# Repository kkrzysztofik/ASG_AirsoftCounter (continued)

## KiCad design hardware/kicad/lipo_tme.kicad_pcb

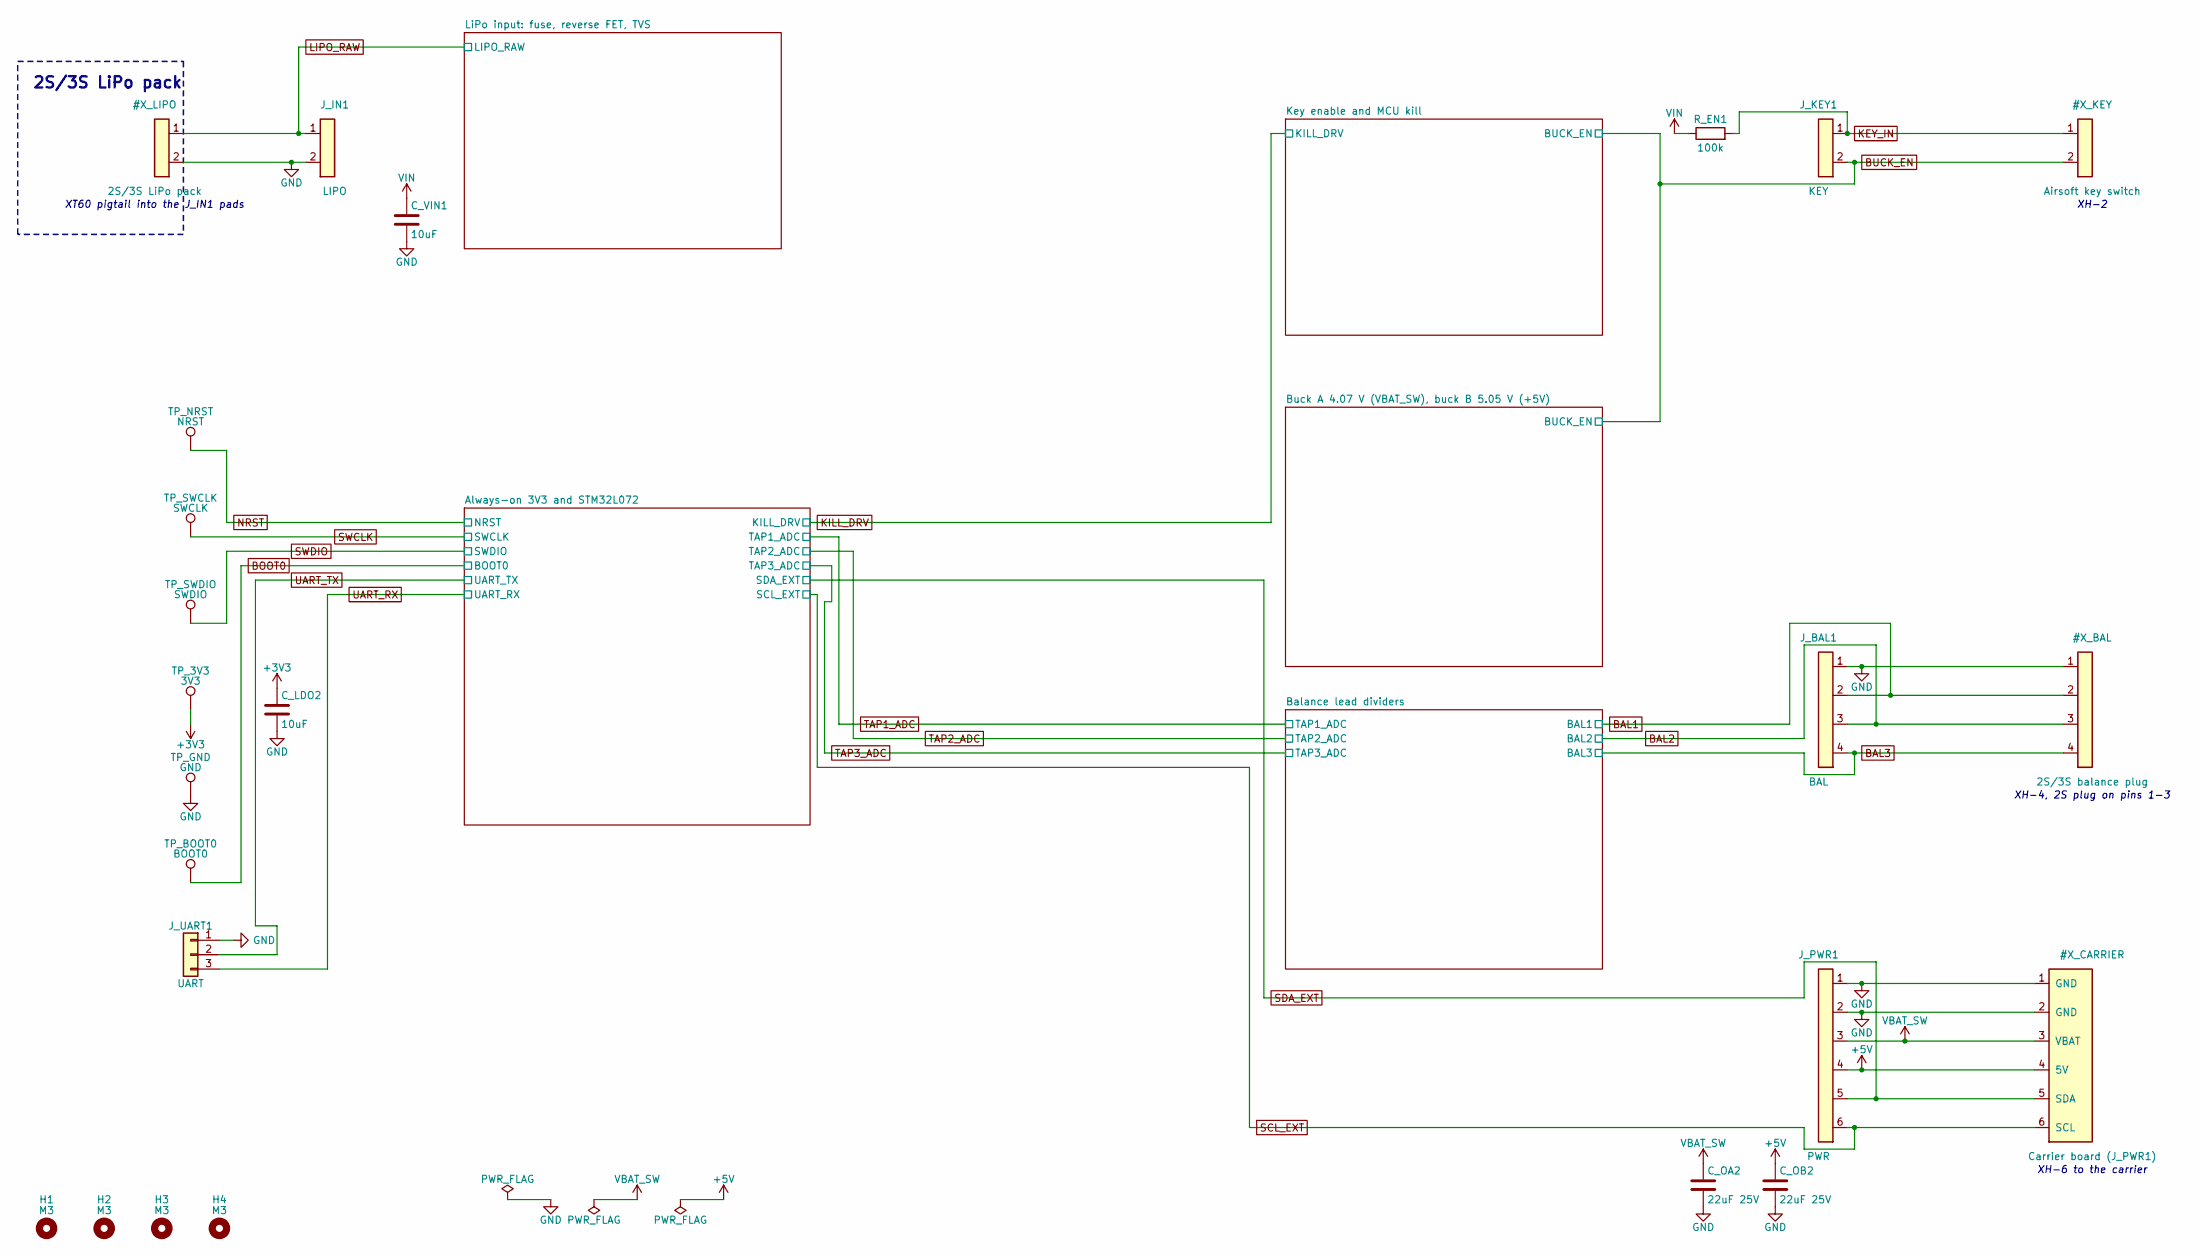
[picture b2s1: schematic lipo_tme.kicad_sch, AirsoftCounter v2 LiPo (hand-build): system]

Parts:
C_LDO2: 10uF; C_0805_2012Metric_Pad1.18x1.45mm_HandSolder
C_OA2: 22uF 25V; C_1206_3216Metric_Pad1.33x1.80mm_HandSolder
C_OB2: 22uF 25V; C_1206_3216Metric_Pad1.33x1.80mm_HandSolder
C_VIN1: 10uF; C_0805_2012Metric_Pad1.18x1.45mm_HandSolder
H1, H2, H3, H4: M3; MountingHole_3.2mm_M3
J_BAL1: BAL; JST_XH_B4B-XH-A_1x04_P2.50mm_Vertical
J_IN1: LIPO; SolderWire-1.5sqmm_1x02_P6mm_D1.7mm_OD3mm
J_KEY1: KEY; JST_XH_B2B-XH-A_1x02_P2.50mm_Vertical
J_PWR1: PWR; JST_XH_B6B-XH-A_1x06_P2.50mm_Vertical
J_UART1: UART; PinHeader_1x03_P2.54mm_Vertical
R_EN1: 100k; R_0805_2012Metric_Pad1.20x1.40mm_HandSolder
TP_3V3: 3V3; TestPoint_Pad_D1.5mm
TP_BOOT0: BOOT0; TestPoint_Pad_D1.5mm
TP_GND: GND; TestPoint_Pad_D1.5mm
TP_NRST: NRST; TestPoint_Pad_D1.5mm
TP_SWCLK: SWCLK; TestPoint_Pad_D1.5mm
TP_SWDIO: SWDIO; TestPoint_Pad_D1.5mm

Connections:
+3V3: C_LDO2.1, TP_3V3.1; also elsewhere on the board
BOOT0: TP_BOOT0.1; also elsewhere on the board
NRST: TP_NRST.1; also elsewhere on the board
SWCLK: TP_SWCLK.1; also elsewhere on the board
SWDIO: TP_SWDIO.1; also elsewhere on the board
UART_RX: J_UART1.3; also elsewhere on the board
UART_TX: J_UART1.2; also elsewhere on the board
VIN: C_VIN1.1, R_EN1.1; also elsewhere on the board

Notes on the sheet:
XH-6 to the carrier
XH-2
XH-4, 2S plug on pins 1-3
XT60 pigtail into the J_IN1 pads
2S/3S LiPo pack

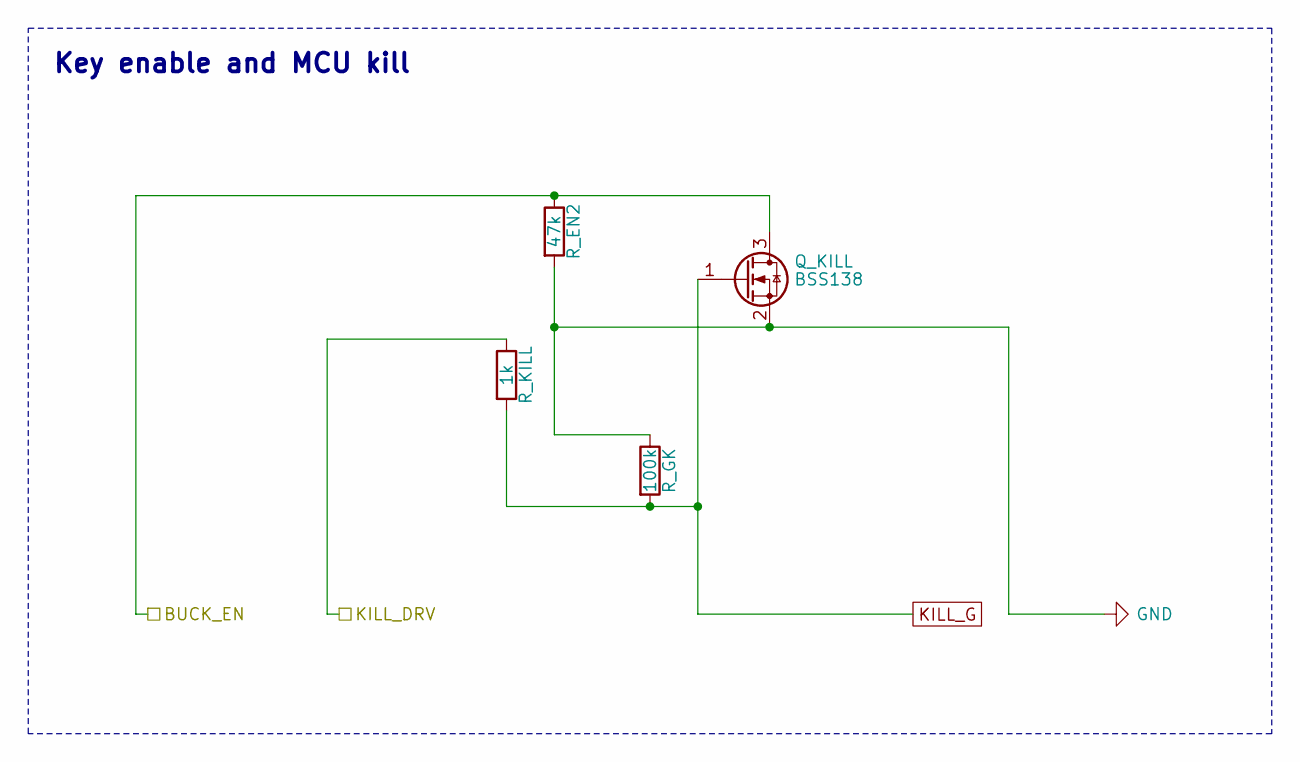
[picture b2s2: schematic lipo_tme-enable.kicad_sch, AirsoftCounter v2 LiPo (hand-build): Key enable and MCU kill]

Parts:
Q_KILL: BSS138; SOT-23
R_EN2: 47k; R_0805_2012Metric_Pad1.20x1.40mm_HandSolder
R_GK: 100k; R_0805_2012Metric_Pad1.20x1.40mm_HandSolder
R_KILL: 1k; R_0805_2012Metric_Pad1.20x1.40mm_HandSolder

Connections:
KILL_DRV: R_KILL.1; also elsewhere on the board
KILL_G: Q_KILL.1 (G), R_GK.2, R_KILL.2

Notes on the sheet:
Key enable and MCU kill

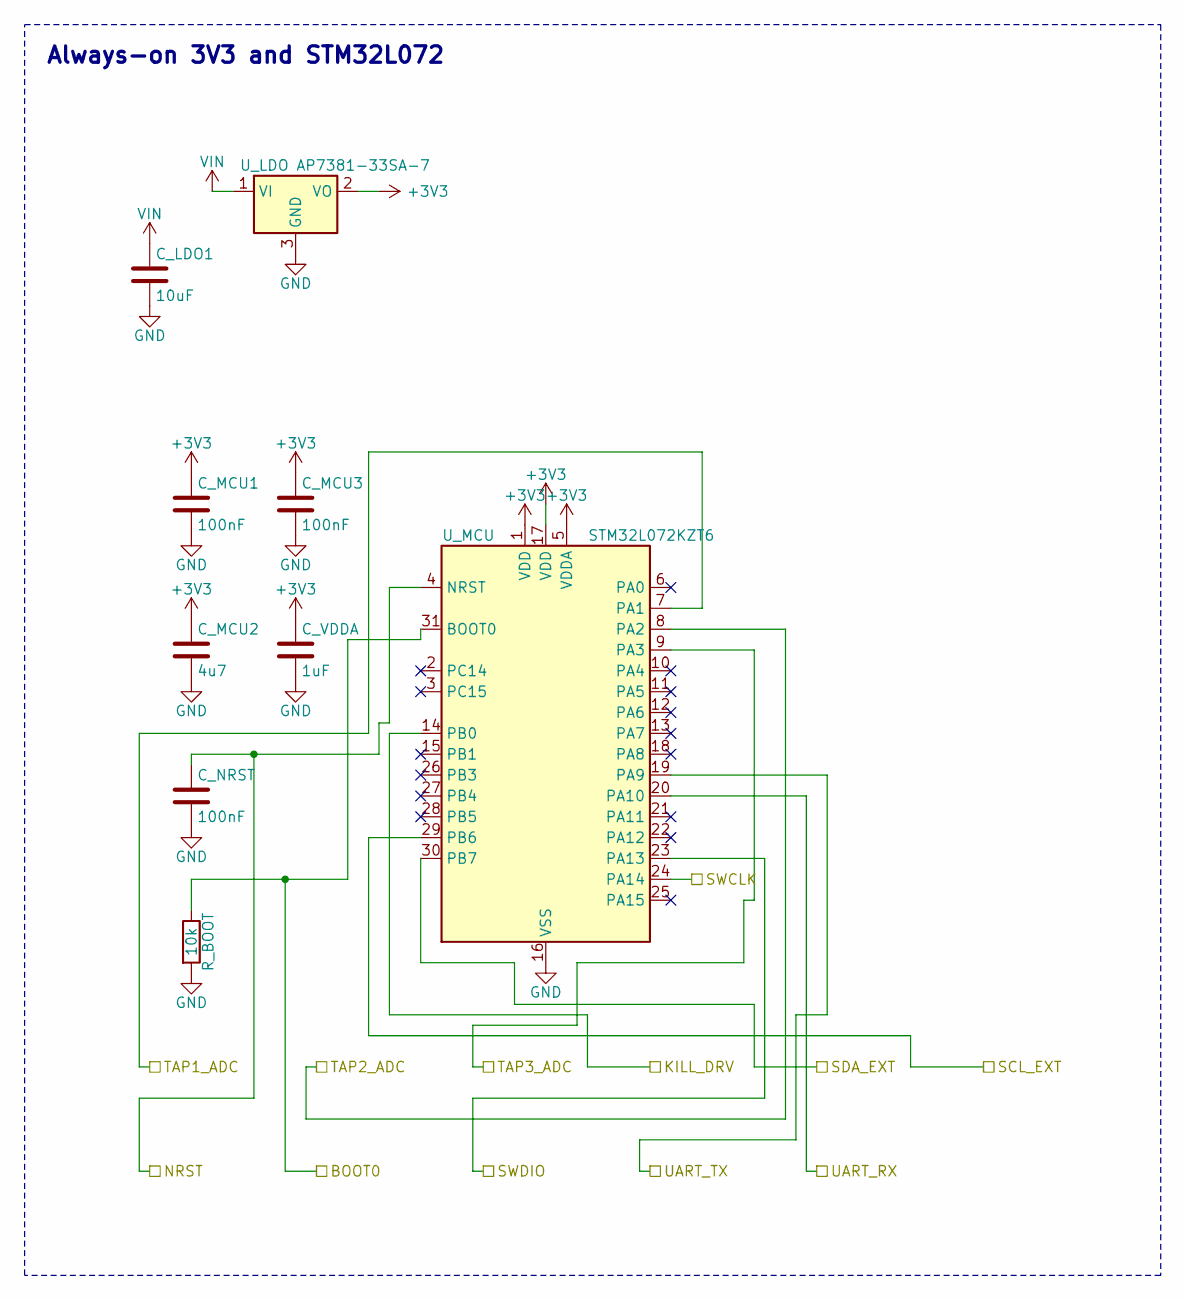
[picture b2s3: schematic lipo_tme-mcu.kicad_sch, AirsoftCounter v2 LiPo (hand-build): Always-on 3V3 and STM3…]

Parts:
C_LDO1: 10uF; C_0805_2012Metric_Pad1.18x1.45mm_HandSolder
C_MCU1, C_MCU3: 100nF; C_0805_2012Metric_Pad1.18x1.45mm_HandSolder
C_MCU2: 4u7; C_0805_2012Metric_Pad1.18x1.45mm_HandSolder
C_NRST: 100nF; C_0805_2012Metric_Pad1.18x1.45mm_HandSolder
C_VDDA: 1uF; C_0805_2012Metric_Pad1.18x1.45mm_HandSolder
R_BOOT: 10k; R_0805_2012Metric_Pad1.20x1.40mm_HandSolder
U_LDO: AP7381-33SA-7; SOT-23
U_MCU: STM32L072KZT6; LQFP-32_7x7mm_P0.8mm

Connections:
+3V3: C_MCU1.1, C_MCU2.1, C_MCU3.1, C_VDDA.1, U_LDO.2 (VO), U_MCU.1 (VDD), U_MCU.5 (VDDA), U_MCU.17 (VDD); also elsewhere on the board
BOOT0: R_BOOT.1, U_MCU.31 (BOOT0); also elsewhere on the board
KILL_DRV: U_MCU.14 (PB0); also elsewhere on the board
NRST: C_NRST.1, U_MCU.4 (NRST); also elsewhere on the board
SWCLK: U_MCU.24 (PA14); also elsewhere on the board
SWDIO: U_MCU.23 (PA13); also elsewhere on the board
TAP1_ADC: U_MCU.7 (PA1); also elsewhere on the board
TAP2_ADC: U_MCU.8 (PA2); also elsewhere on the board
TAP3_ADC: U_MCU.9 (PA3); also elsewhere on the board
UART_RX: U_MCU.20 (PA10); also elsewhere on the board
UART_TX: U_MCU.19 (PA9); also elsewhere on the board
VIN: C_LDO1.1, U_LDO.1 (VI); also elsewhere on the board

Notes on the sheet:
Always-on 3V3 and STM32L072

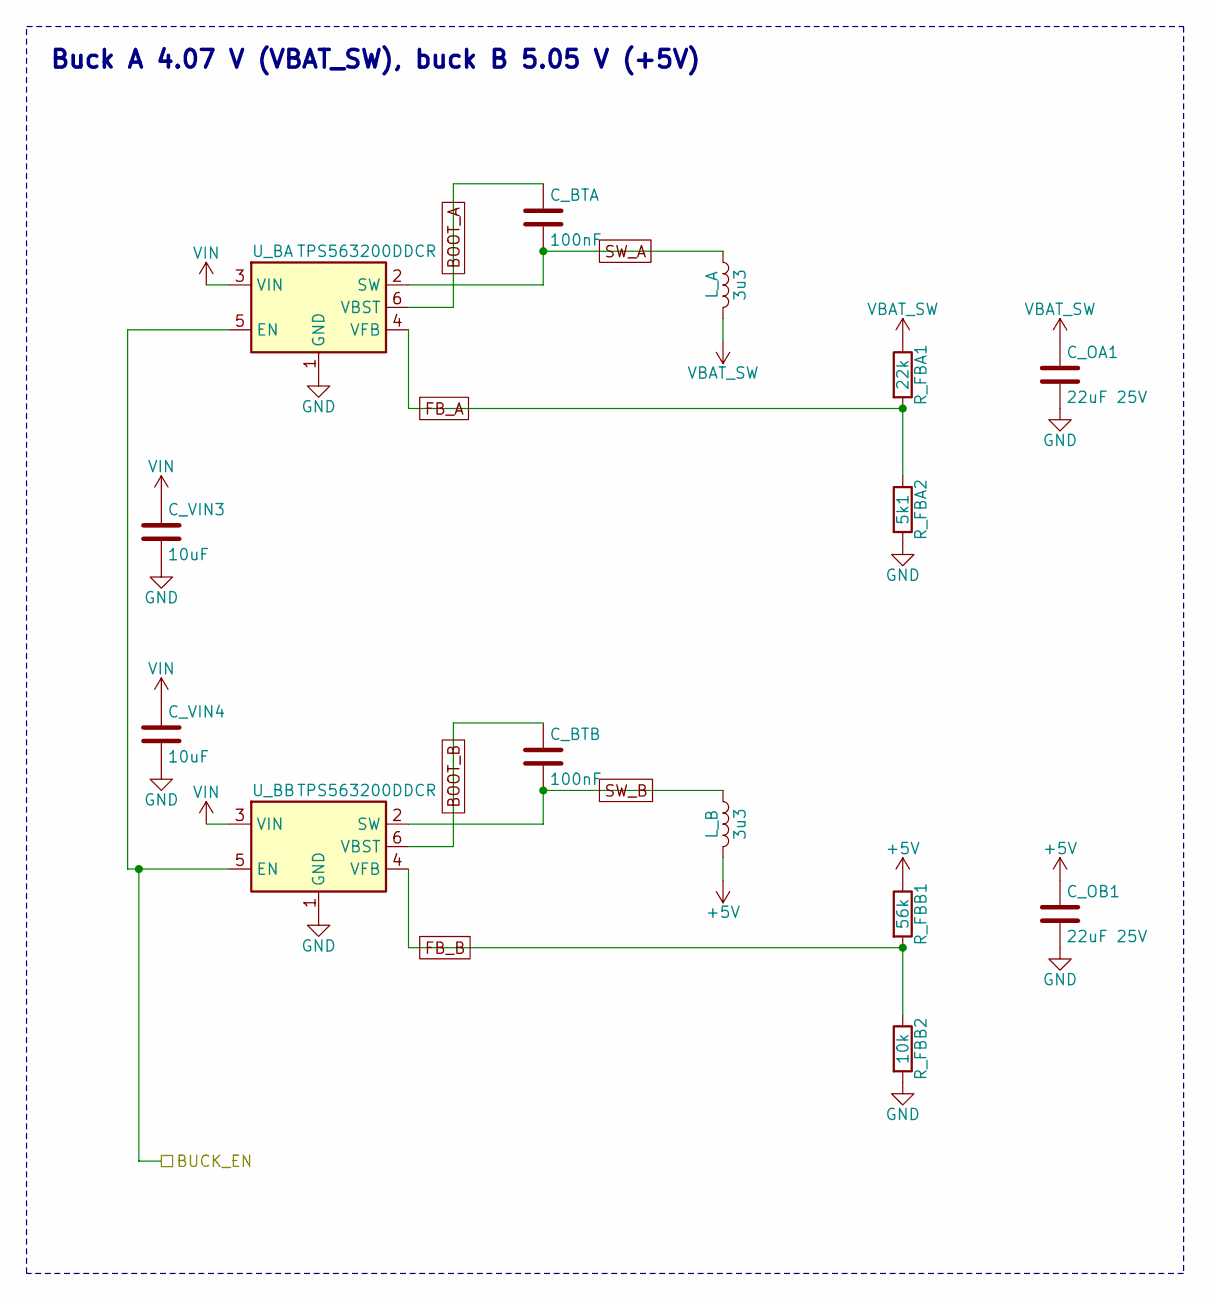
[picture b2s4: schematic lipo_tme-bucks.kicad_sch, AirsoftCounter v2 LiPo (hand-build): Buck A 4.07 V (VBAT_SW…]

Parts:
C_BTA: 100nF; C_0805_2012Metric_Pad1.18x1.45mm_HandSolder
C_BTB: 100nF; C_0805_2012Metric_Pad1.18x1.45mm_HandSolder
C_OA1: 22uF 25V; C_1206_3216Metric_Pad1.33x1.80mm_HandSolder
C_OB1: 22uF 25V; C_1206_3216Metric_Pad1.33x1.80mm_HandSolder
C_VIN3, C_VIN4: 10uF; C_0805_2012Metric_Pad1.18x1.45mm_HandSolder
L_A: 3u3; L_Bourns_SRN6045TA
L_B: 3u3; L_Bourns_SRN6045TA
R_FBA1: 22k; R_0805_2012Metric_Pad1.20x1.40mm_HandSolder
R_FBA2: 5k1; R_0805_2012Metric_Pad1.20x1.40mm_HandSolder
R_FBB1: 56k; R_0805_2012Metric_Pad1.20x1.40mm_HandSolder
R_FBB2: 10k; R_0805_2012Metric_Pad1.20x1.40mm_HandSolder
U_BA: TPS563200DDCR; TSOT-23-6
U_BB: TPS563200DDCR; TSOT-23-6

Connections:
BOOT_A: C_BTA.1, U_BA.6 (VBST)
BOOT_B: C_BTB.1, U_BB.6 (VBST)
FB_A: R_FBA1.2, R_FBA2.1, U_BA.4 (VFB)
FB_B: R_FBB1.2, R_FBB2.1, U_BB.4 (VFB)
SW_A: C_BTA.2, L_A.1, U_BA.2 (SW)
SW_B: C_BTB.2, L_B.1, U_BB.2 (SW)
VIN: C_VIN3.1, C_VIN4.1, U_BA.3 (VIN), U_BB.3 (VIN); also elsewhere on the board

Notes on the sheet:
Buck A 4.07 V (VBAT_SW), buck B 5.05 V (+5V)

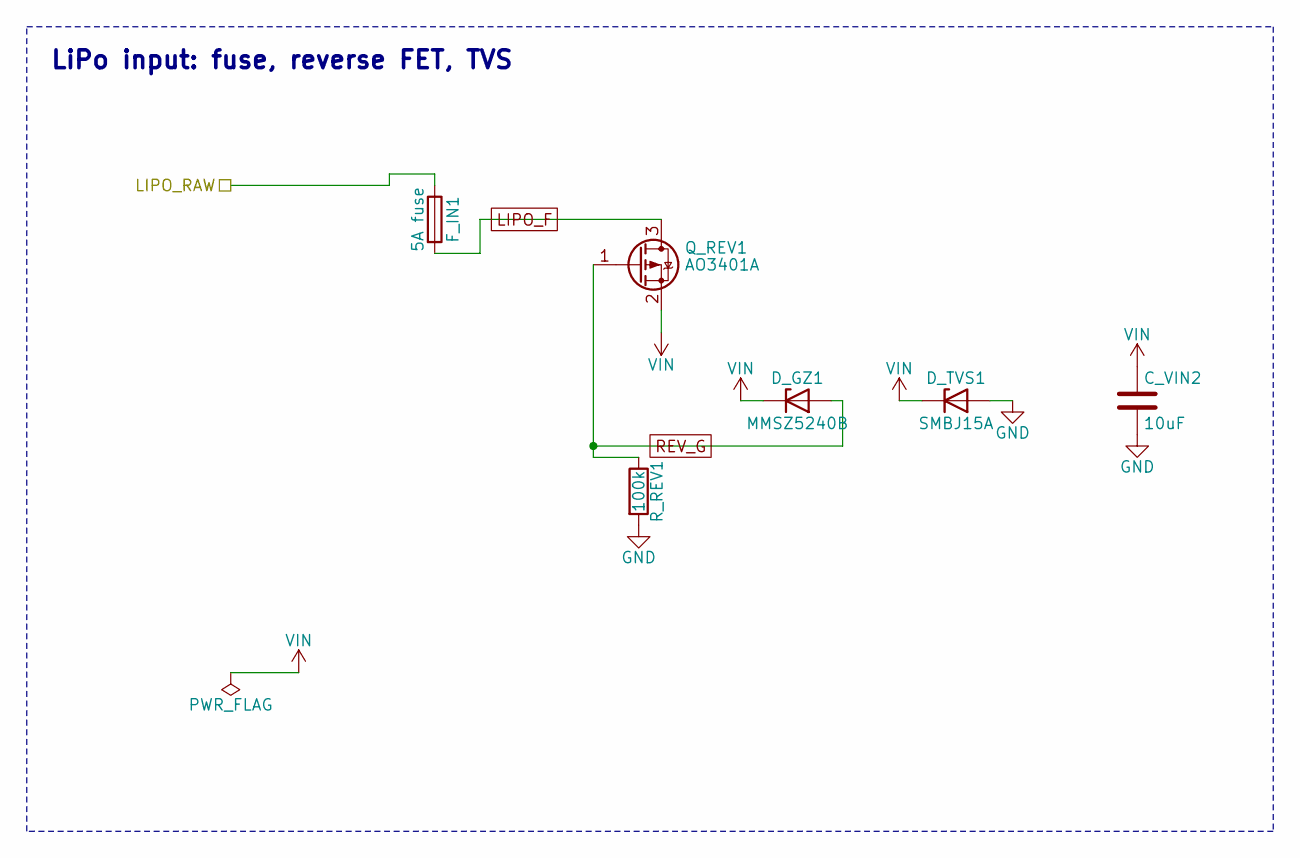
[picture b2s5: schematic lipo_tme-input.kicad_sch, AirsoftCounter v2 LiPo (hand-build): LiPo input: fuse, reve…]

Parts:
C_VIN2: 10uF; C_0805_2012Metric_Pad1.18x1.45mm_HandSolder
D_GZ1: MMSZ5240B; D_SOD-123
D_TVS1: SMBJ15A; D_SMB
F_IN1: 5A fuse; Fuse_1206_3216Metric_Pad1.42x1.75mm_HandSolder
Q_REV1: AO3401A; SOT-23
R_REV1: 100k; R_0805_2012Metric_Pad1.20x1.40mm_HandSolder

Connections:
LIPO_F: F_IN1.2, Q_REV1.3 (D)
REV_G: D_GZ1.2 (A), Q_REV1.1 (G), R_REV1.1
VIN: C_VIN2.1, D_GZ1.1 (K), D_TVS1.1 (K), Q_REV1.2 (S); also elsewhere on the board

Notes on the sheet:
LiPo input: fuse, reverse FET, TVS

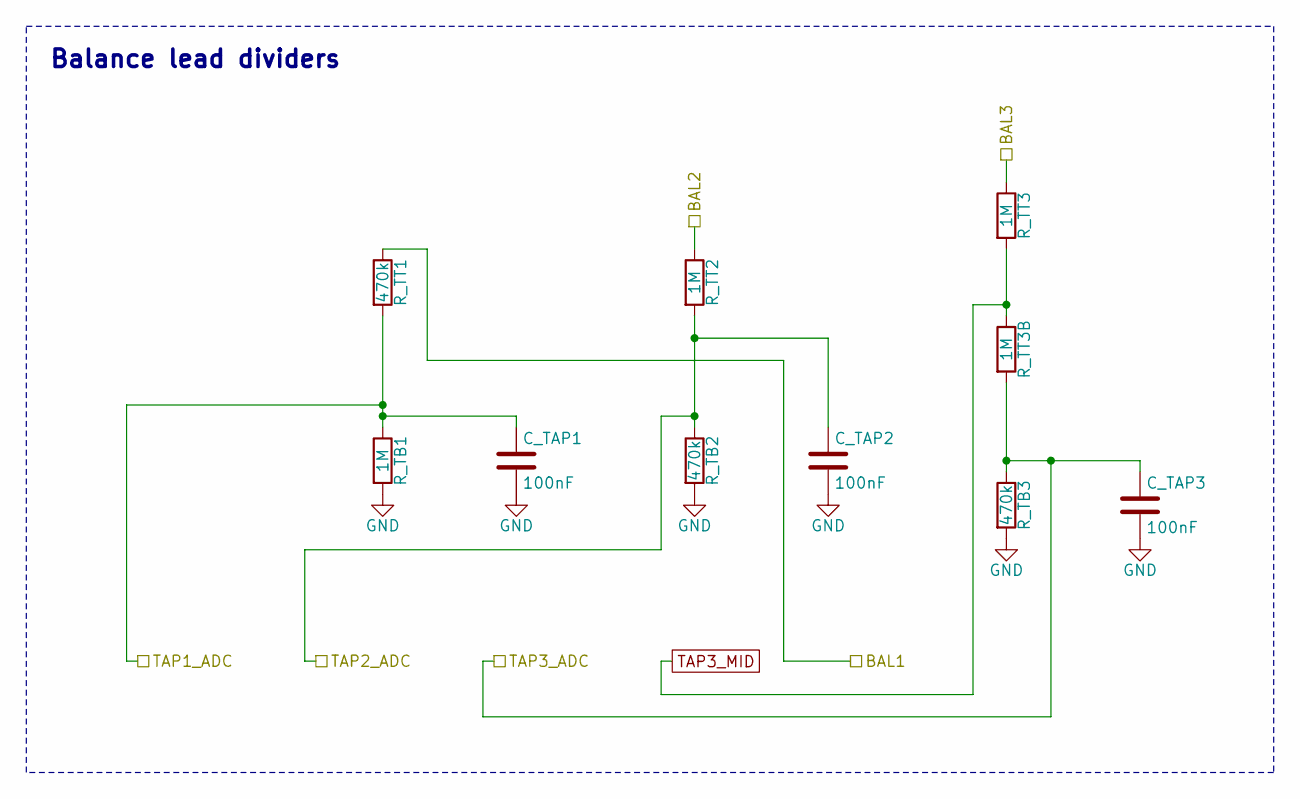
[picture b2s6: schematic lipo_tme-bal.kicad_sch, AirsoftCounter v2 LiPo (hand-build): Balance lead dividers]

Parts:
C_TAP1, C_TAP2, C_TAP3: 100nF; C_0805_2012Metric_Pad1.18x1.45mm_HandSolder
R_TB1: 1M; R_0805_2012Metric_Pad1.20x1.40mm_HandSolder
R_TB2, R_TB3: 470k; R_0805_2012Metric_Pad1.20x1.40mm_HandSolder
R_TT1: 470k; R_0805_2012Metric_Pad1.20x1.40mm_HandSolder
R_TT2, R_TT3, R_TT3B: 1M; R_0805_2012Metric_Pad1.20x1.40mm_HandSolder

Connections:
TAP1_ADC: C_TAP1.1, R_TB1.1, R_TT1.2; also elsewhere on the board
TAP2_ADC: C_TAP2.1, R_TB2.1, R_TT2.2; also elsewhere on the board
TAP3_ADC: C_TAP3.1, R_TB3.1, R_TT3B.2; also elsewhere on the board
TAP3_MID: R_TT3.2, R_TT3B.1

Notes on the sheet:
Balance lead dividers

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
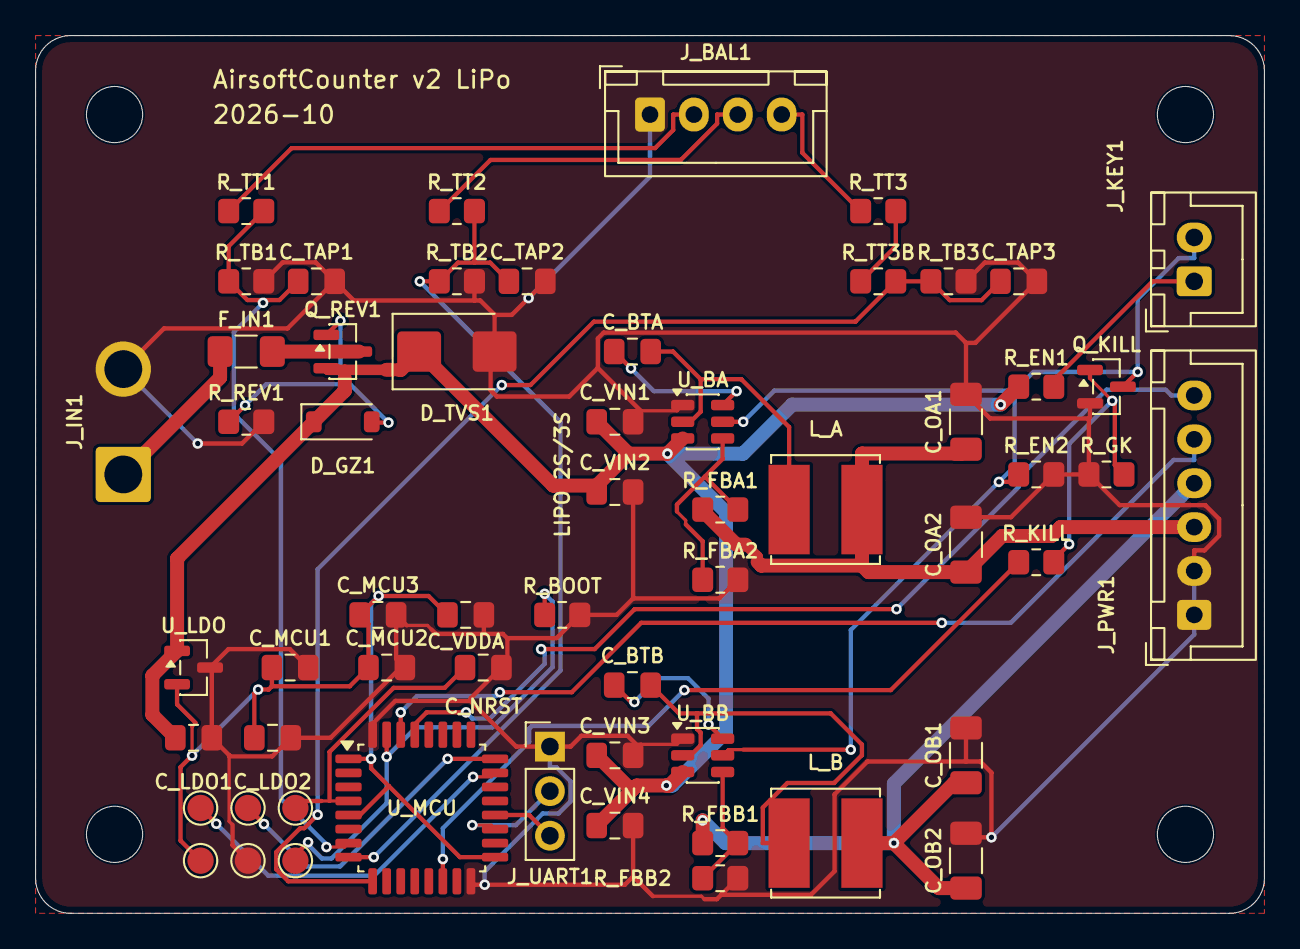
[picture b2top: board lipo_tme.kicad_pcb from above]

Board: 2 copper layers, 70.0 x 50.0 mm, 63 parts (0 on the bottom side), 33 nets.

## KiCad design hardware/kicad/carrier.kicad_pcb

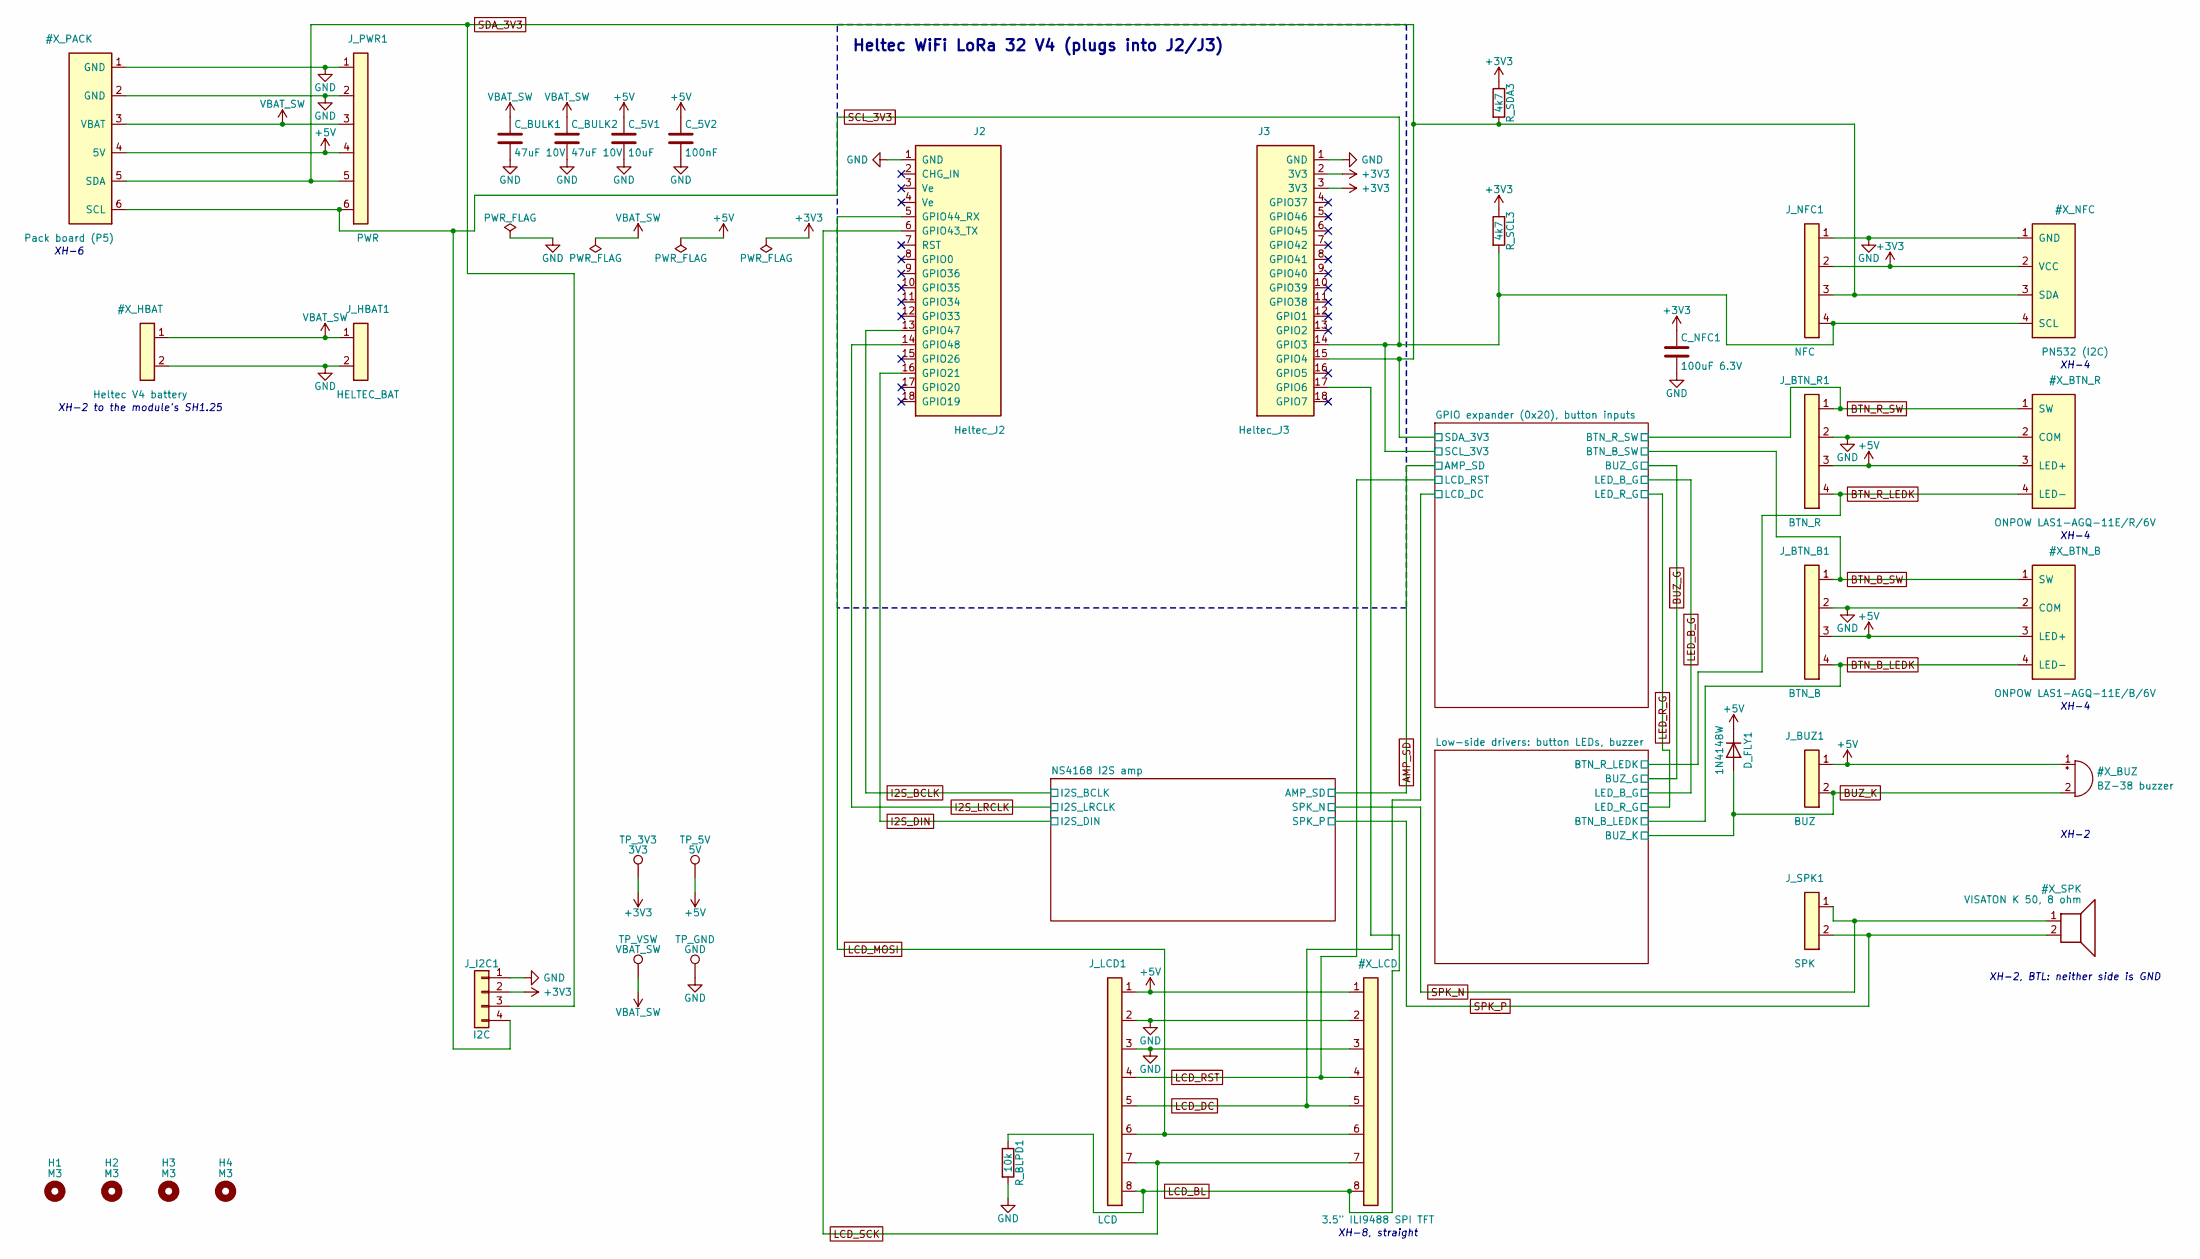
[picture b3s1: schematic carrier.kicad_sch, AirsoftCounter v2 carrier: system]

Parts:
C_5V1: 10uF; C_0805_2012Metric_Pad1.18x1.45mm_HandSolder
C_5V2: 100nF; C_0805_2012Metric_Pad1.18x1.45mm_HandSolder
C_BULK1, C_BULK2: 47uF 10V; C_1206_3216Metric_Pad1.33x1.80mm_HandSolder
C_NFC1: 100uF 6.3V; C_1206_3216Metric_Pad1.33x1.80mm_HandSolder
D_FLY1: 1N4148W; D_SOD-123
H1, H2, H3, H4: M3; MountingHole_3.2mm_M3
J2: Heltec_J2; PinSocket_1x18_P2.54mm_Vertical
J3: Heltec_J3; PinSocket_1x18_P2.54mm_Vertical
J_BTN_B1: BTN_B; JST_XH_B4B-XH-A_1x04_P2.50mm_Vertical
J_BTN_R1: BTN_R; JST_XH_B4B-XH-A_1x04_P2.50mm_Vertical
J_BUZ1: BUZ; JST_XH_B2B-XH-A_1x02_P2.50mm_Vertical
J_HBAT1: HELTEC_BAT; JST_XH_B2B-XH-A_1x02_P2.50mm_Vertical
J_I2C1: I2C; PinHeader_1x04_P2.54mm_Vertical
J_LCD1: LCD; JST_XH_B8B-XH-A_1x08_P2.50mm_Vertical
J_NFC1: NFC; JST_XH_B4B-XH-A_1x04_P2.50mm_Vertical
J_PWR1: PWR; JST_XH_B6B-XH-A_1x06_P2.50mm_Vertical
J_SPK1: SPK; JST_XH_B2B-XH-A_1x02_P2.50mm_Vertical
R_BLPD1: 10k; R_0805_2012Metric_Pad1.20x1.40mm_HandSolder
R_SCL3: 4k7; R_0805_2012Metric_Pad1.20x1.40mm_HandSolder
R_SDA3: 4k7; R_0805_2012Metric_Pad1.20x1.40mm_HandSolder
TP_3V3: 3V3; TestPoint_Pad_D1.5mm
TP_5V: 5V; TestPoint_Pad_D1.5mm
TP_GND: GND; TestPoint_Pad_D1.5mm
TP_VSW: VBAT_SW; TestPoint_Pad_D1.5mm

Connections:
I2S_BCLK: J2.13 (GPIO47); also elsewhere on the board
I2S_DIN: J2.16 (GPIO21); also elsewhere on the board
I2S_LRCLK: J2.14 (GPIO48); also elsewhere on the board

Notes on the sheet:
XH-8, straight
XH-4
XH-2
XH-2, BTL: neither side is GND
XH-6
Heltec WiFi LoRa 32 V4 (plugs into J2/J3)
XH-2 to the module's SH1.25

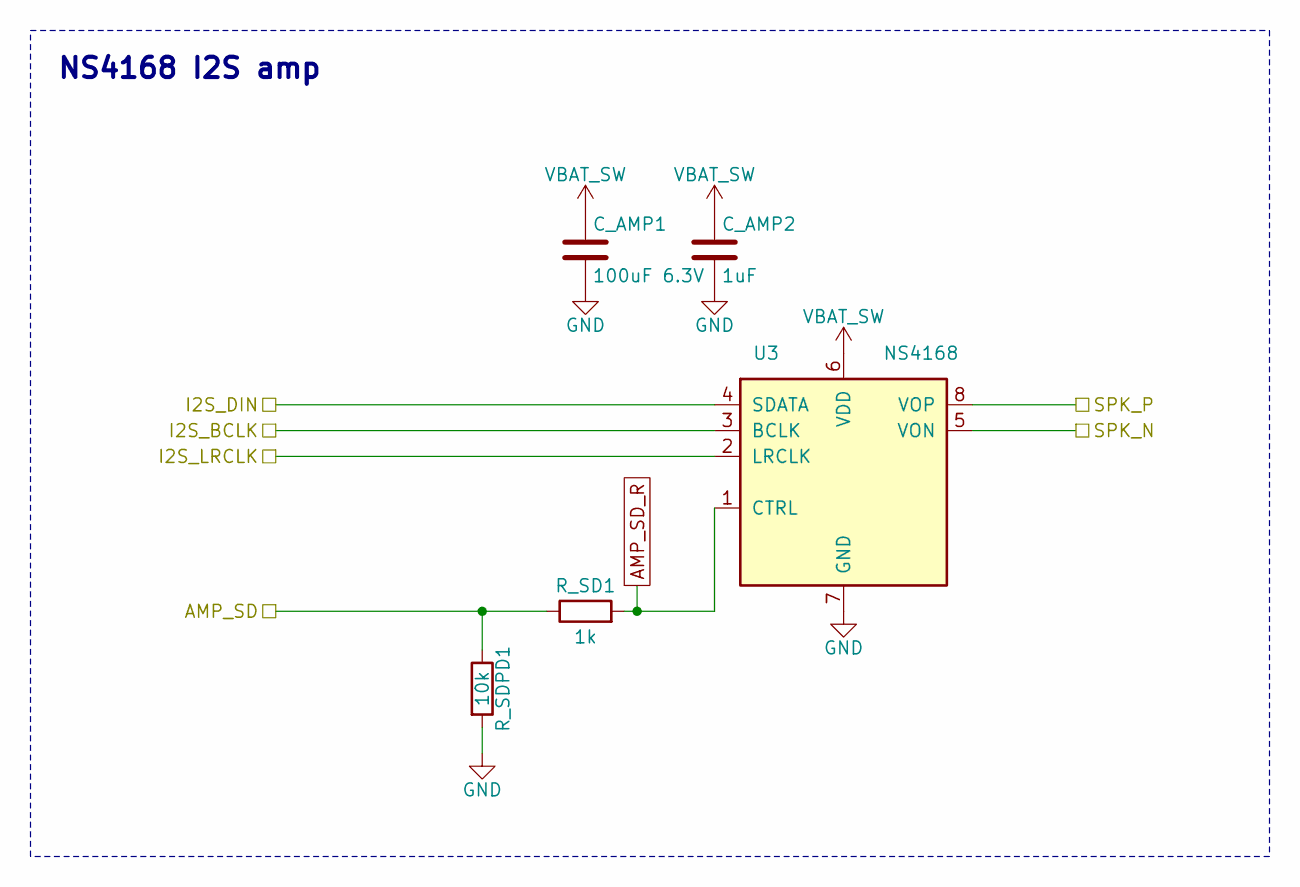
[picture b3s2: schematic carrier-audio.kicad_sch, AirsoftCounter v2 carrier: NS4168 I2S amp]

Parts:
C_AMP1: 100uF 6.3V; C_1206_3216Metric_Pad1.33x1.80mm_HandSolder
C_AMP2: 1uF; C_0805_2012Metric_Pad1.18x1.45mm_HandSolder
R_SD1: 1k; R_0805_2012Metric_Pad1.20x1.40mm_HandSolder
R_SDPD1: 10k; R_0805_2012Metric_Pad1.20x1.40mm_HandSolder
U3: NS4168; HSOP-8-1EP_3.9x4.9mm_P1.27mm_EP2.3x2.3mm_ThermalVias

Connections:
AMP_SD: R_SD1.1, R_SDPD1.1; also elsewhere on the board
AMP_SD_R: R_SD1.2, U3.1 (CTRL)
I2S_BCLK: U3.3 (BCLK); also elsewhere on the board
I2S_DIN: U3.4 (SDATA); also elsewhere on the board
I2S_LRCLK: U3.2 (LRCLK); also elsewhere on the board

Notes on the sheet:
NS4168 I2S amp

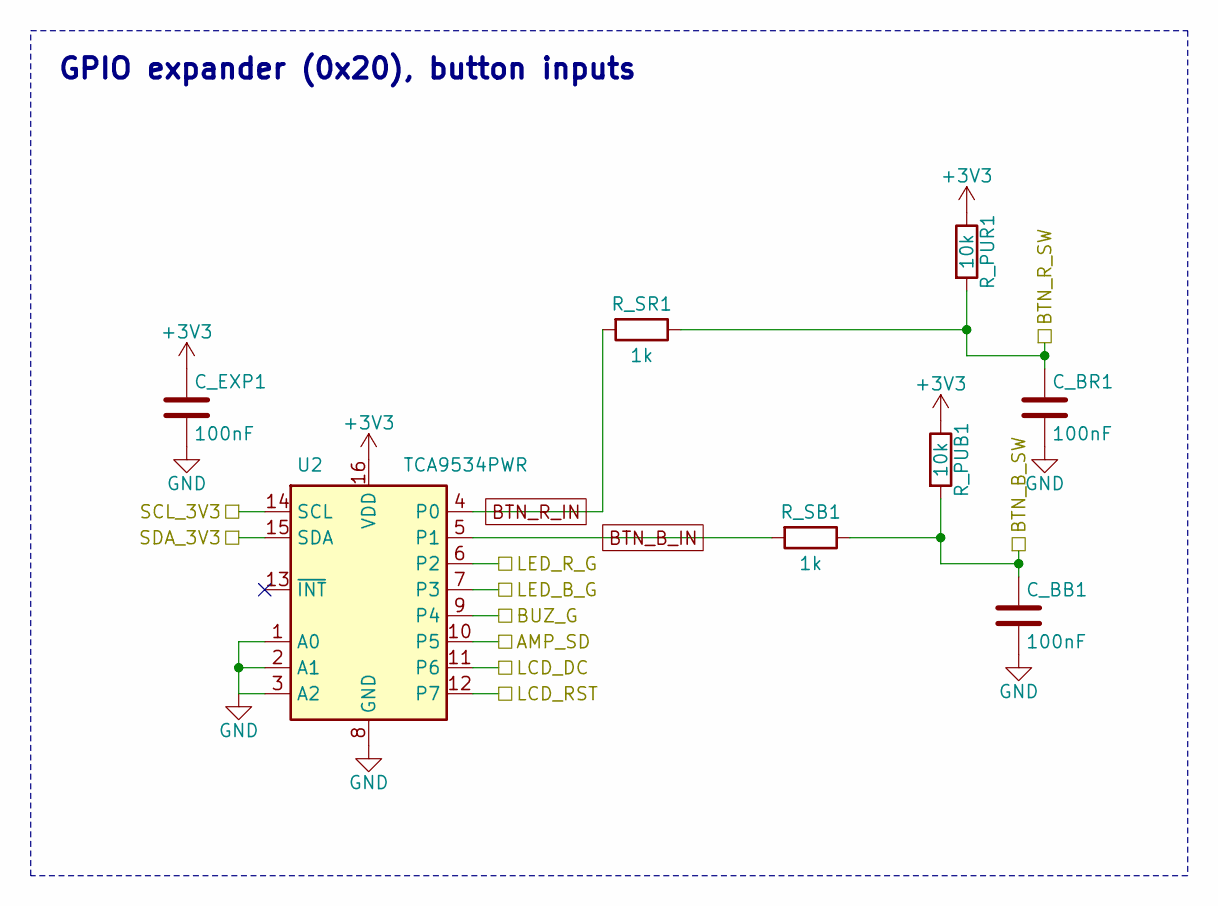
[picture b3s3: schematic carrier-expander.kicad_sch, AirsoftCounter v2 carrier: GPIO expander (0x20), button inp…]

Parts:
C_BB1: 100nF; C_0805_2012Metric_Pad1.18x1.45mm_HandSolder
C_BR1: 100nF; C_0805_2012Metric_Pad1.18x1.45mm_HandSolder
C_EXP1: 100nF; C_0805_2012Metric_Pad1.18x1.45mm_HandSolder
R_PUB1: 10k; R_0805_2012Metric_Pad1.20x1.40mm_HandSolder
R_PUR1: 10k; R_0805_2012Metric_Pad1.20x1.40mm_HandSolder
R_SB1: 1k; R_0805_2012Metric_Pad1.20x1.40mm_HandSolder
R_SR1: 1k; R_0805_2012Metric_Pad1.20x1.40mm_HandSolder
U2: TCA9534PWR; TSSOP-16_4.4x5mm_P0.65mm

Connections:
AMP_SD: U2.10 (P5); also elsewhere on the board
BTN_B_IN: R_SB1.2, U2.5 (P1)
BTN_R_IN: R_SR1.2, U2.4 (P0)
BUZ_G: U2.9 (P4); also elsewhere on the board
LED_B_G: U2.7 (P3); also elsewhere on the board
LED_R_G: U2.6 (P2); also elsewhere on the board

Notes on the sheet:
GPIO expander (0x20), button inputs

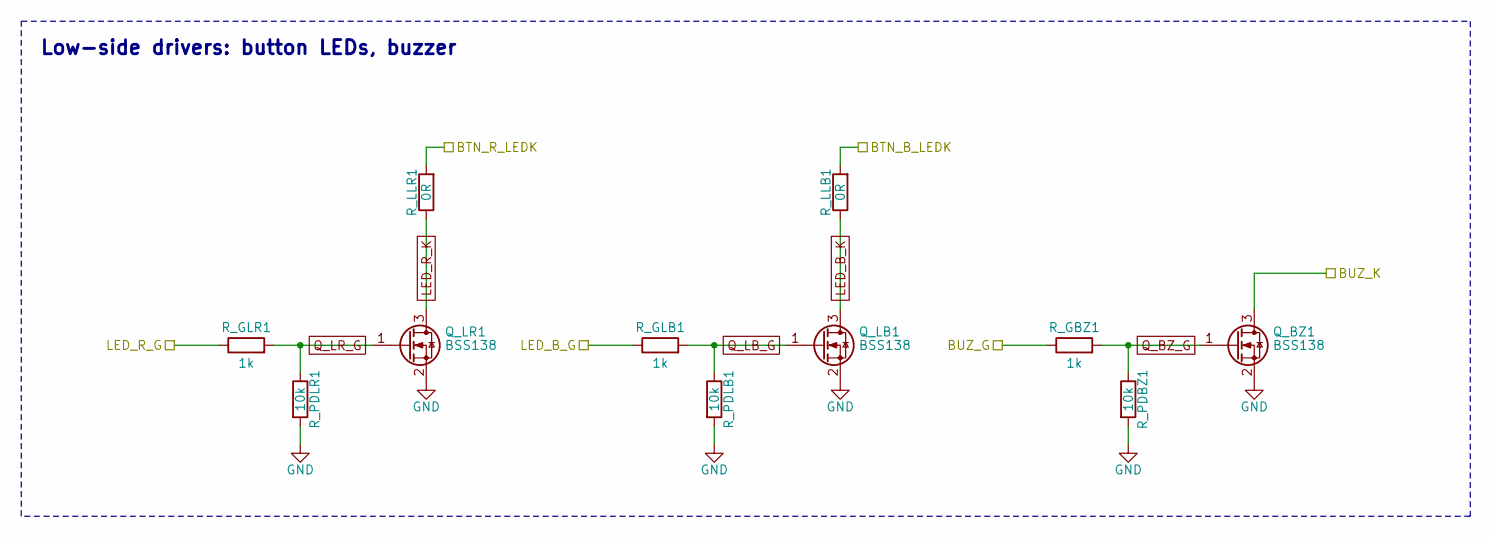
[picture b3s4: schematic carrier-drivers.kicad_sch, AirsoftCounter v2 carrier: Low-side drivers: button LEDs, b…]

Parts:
Q_BZ1: BSS138; SOT-23
Q_LB1: BSS138; SOT-23
Q_LR1: BSS138; SOT-23
R_GBZ1: 1k; R_0805_2012Metric_Pad1.20x1.40mm_HandSolder
R_GLB1: 1k; R_0805_2012Metric_Pad1.20x1.40mm_HandSolder
R_GLR1: 1k; R_0805_2012Metric_Pad1.20x1.40mm_HandSolder
R_LLB1: 0R; R_0805_2012Metric_Pad1.20x1.40mm_HandSolder
R_LLR1: 0R; R_0805_2012Metric_Pad1.20x1.40mm_HandSolder
R_PDBZ1: 10k; R_0805_2012Metric_Pad1.20x1.40mm_HandSolder
R_PDLB1: 10k; R_0805_2012Metric_Pad1.20x1.40mm_HandSolder
R_PDLR1: 10k; R_0805_2012Metric_Pad1.20x1.40mm_HandSolder

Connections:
BUZ_G: R_GBZ1.1; also elsewhere on the board
LED_B_G: R_GLB1.1; also elsewhere on the board
LED_B_K: Q_LB1.3 (D), R_LLB1.1
LED_R_G: R_GLR1.1; also elsewhere on the board
LED_R_K: Q_LR1.3 (D), R_LLR1.1
Q_BZ_G: Q_BZ1.1 (G), R_GBZ1.2, R_PDBZ1.1
Q_LB_G: Q_LB1.1 (G), R_GLB1.2, R_PDLB1.1
Q_LR_G: Q_LR1.1 (G), R_GLR1.2, R_PDLR1.1

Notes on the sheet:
Low-side drivers: button LEDs, buzzer

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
